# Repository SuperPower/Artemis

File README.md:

# SuperPower
Here you should find the best power supplies for your low-power projects. Because of different requirements for an Raspberry Pi and micro-controllers like the ESP32 we split the project into two boards, one for the Raspberry Pi (SuperPower-Rpi) and one for micro-controllers (SuperPower-uC) with low power.

##### [SuperPower-Rpi](/SuperPower-RPi/) for Raspberry Pi

##### [SuperPower-uC](https://github.com/SuperPower) for micro-controllers and low-power devices

## Licence

All hardware designs and products you can find in this repository is licensed under [CERN Open Hardware Licence Version 2 - Weakly Reciprocal](/LICENCE.txt)

## Relevant links

[Discord Channel](https://discord.gg/dCr86Hk)  

[Google Drive Project Files](https://drive.google.com/drive/folders/1lCirijHUkISdUYBIRblkILHM6fstifWS)

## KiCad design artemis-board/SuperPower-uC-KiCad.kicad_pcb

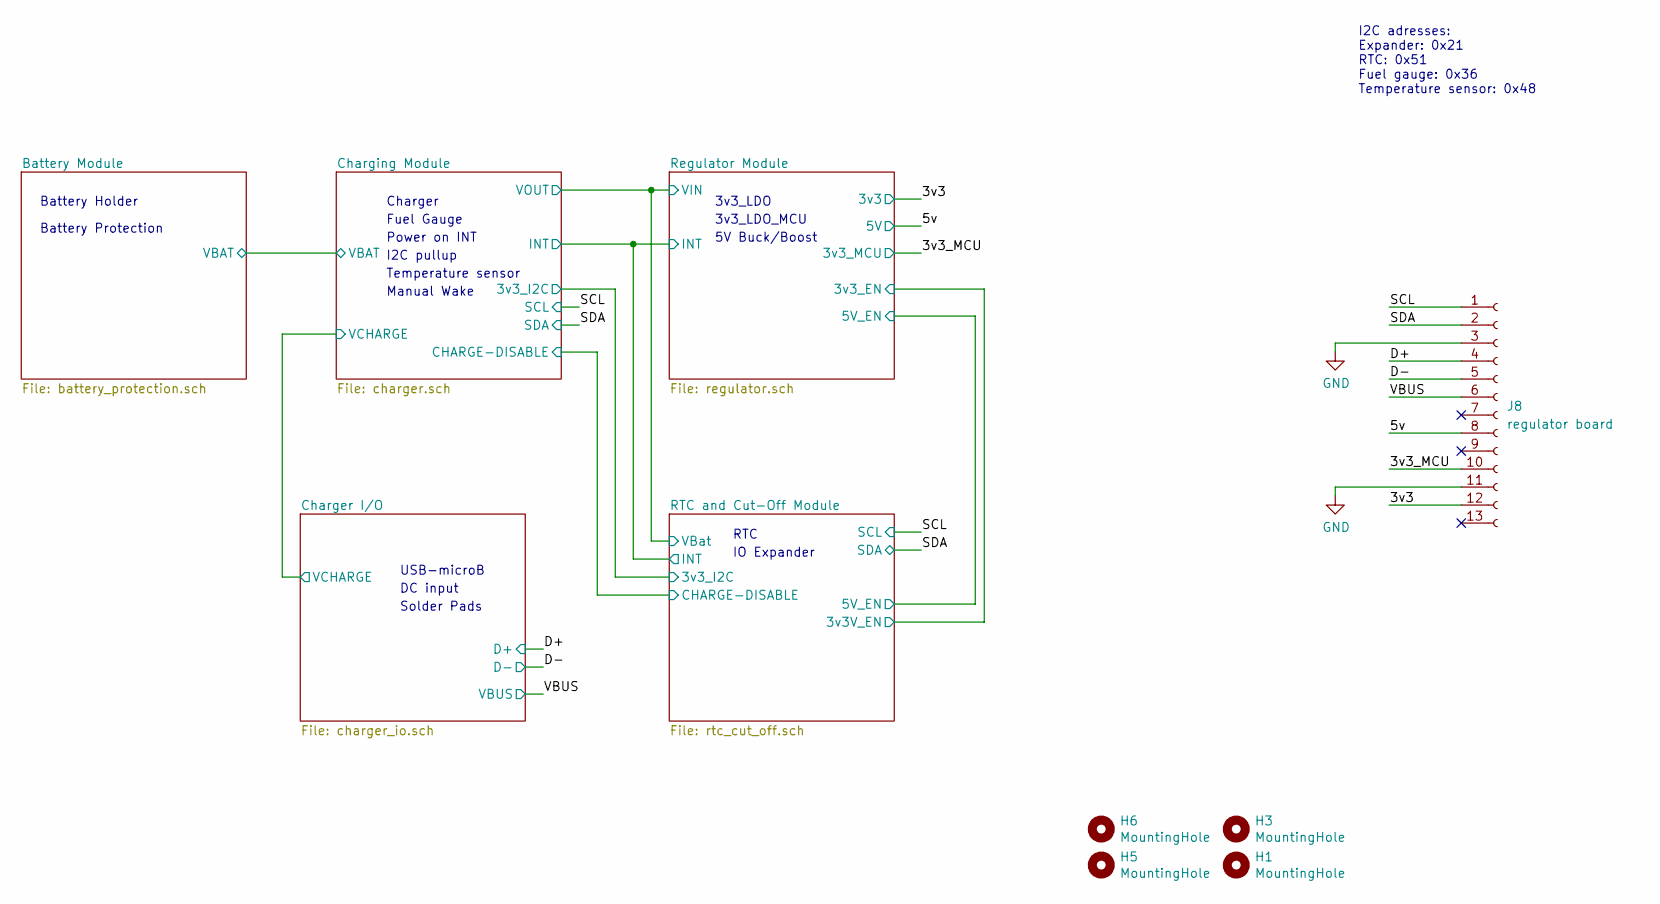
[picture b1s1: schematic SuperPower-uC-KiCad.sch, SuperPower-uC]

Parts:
H1, H3, H5, H6: MountingHole; MountingHole_2.7mm_M2.5_ISO7380
J8: regulator board; PinSocket_1x13_P2.54mm_Vertical; LCSC C52709

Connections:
/3v3: J8.12; also elsewhere on the board
/3v3_MCU: J8.10; also elsewhere on the board
/5v: J8.8; also elsewhere on the board
/D+: J8.4; also elsewhere on the board
/D-: J8.5; also elsewhere on the board
/SCL: J8.1; also elsewhere on the board
/SDA: J8.2; also elsewhere on the board
/VBUS: J8.6; also elsewhere on the board
GND: J8.3, J8.11; also elsewhere on the board

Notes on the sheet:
Battery Holder
Battery Protection
Charger
Fuel Gauge
3v3_LDO
3v3_LDO_MCU
5V Buck/Boost
RTC
USB-microB
DC input
Solder Pads
Manual Wake
Power on INT
IO Expander
I2C pullup
I2C adresses: Expander: 0x21 RTC: 0x51 Fuel gauge: 0x36 Temperature sensor: 0x48
Temperature sensor

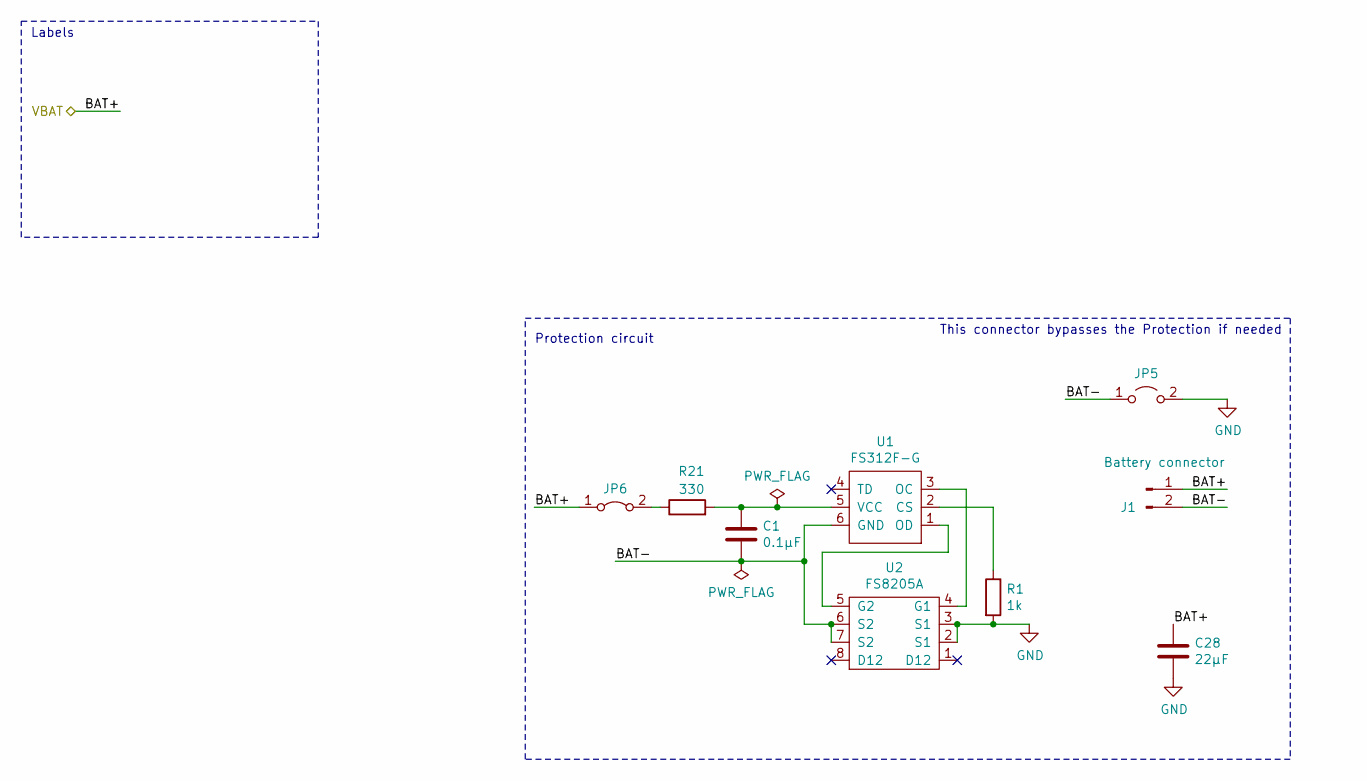
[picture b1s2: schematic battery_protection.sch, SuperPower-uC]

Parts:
C1: 0.1µF; C_0603_1608Metric_Pad1.05x0.95mm_HandSolder; LCSC C14858
C28: 22µF; C_0805_2012Metric; LCSC C45783
J1: Battery connector; JST_PH_S2B-PH-K_1x02_P2.00mm_Horizontal; LCSC C157932
JP5: Jumper_2_Open; SolderJumper-2_P1.3mm_Open_Pad1.0x1.5mm
JP6: Jumper_2_Bridged; SolderJumper-2_P1.3mm_Bridged_Pad1.0x1.5mm
R1: 1k; R_0603_1608Metric_Pad1.05x0.95mm_HandSolder; LCSC C21190
R21: 330; R_0603_1608Metric_Pad1.05x0.95mm_HandSolder; LCSC C23138
U1: FS312F-G; SOT-23-6; LCSC C82736
U2: FS8205A; TSSOP-8_4.4x3mm_P0.65mm; LCSC C16052

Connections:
/Battery Module/BAT-: C1.2, J1.2, JP5.1 (A), U1.6 (GND), U2.6 (S2), U2.7 (S2)
/Battery Module/VBAT: C28.1, J1.1, JP6.1 (A); also elsewhere on the board
GND: C28.2, JP5.2 (B), R1.2, U2.2 (S1), U2.3 (S1); also elsewhere on the board
unnamed: C1.1, R21.2, U1.5 (VCC)
unnamed: JP6.2 (B), R21.1
unnamed: R1.1, U1.2 (CS)
unnamed: U1.1 (OD), U2.5 (G2)
unnamed: U1.3 (OC), U2.4 (G1)

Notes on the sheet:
Protection circuit
Labels
This connector bypasses the Protection if needed

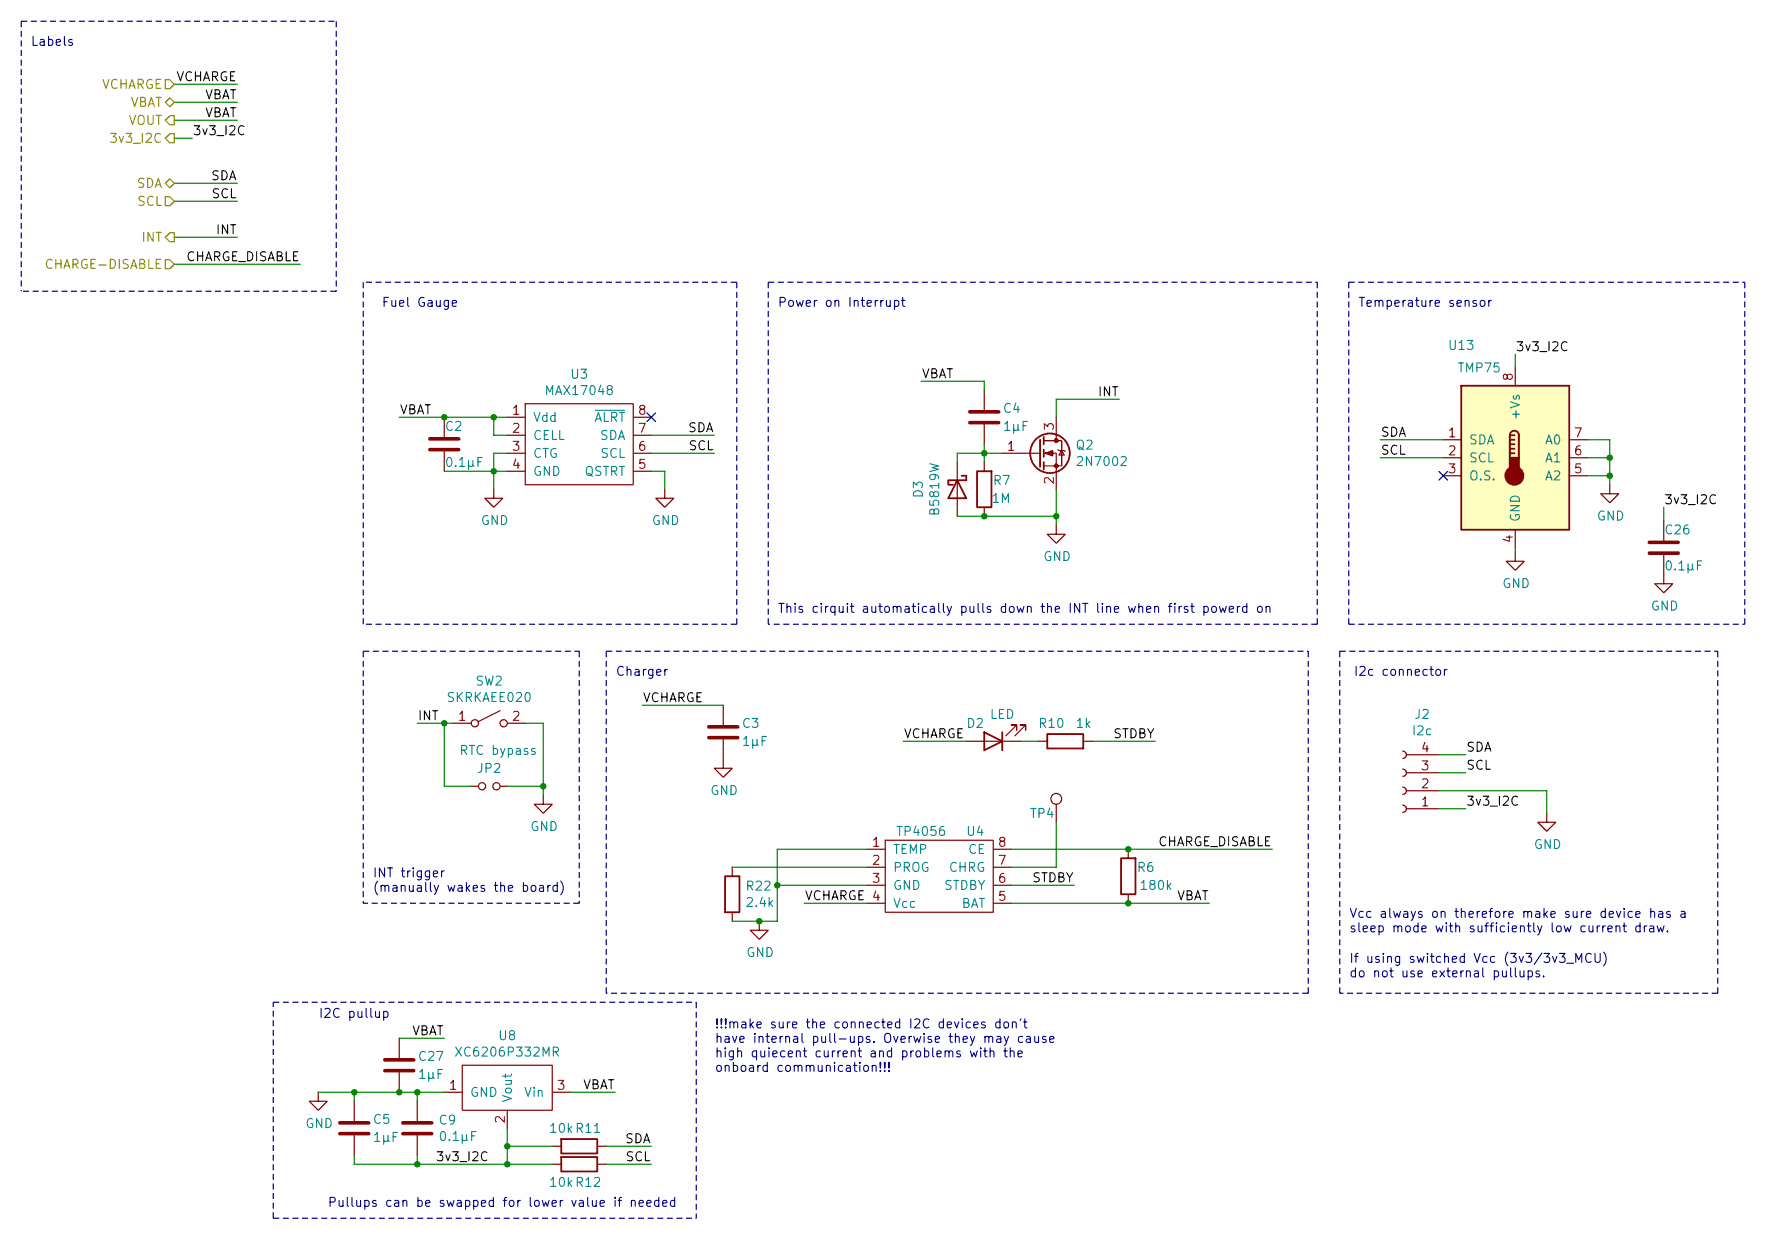
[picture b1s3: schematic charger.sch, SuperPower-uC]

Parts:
C2, C9, C26: 0.1µF; C_0603_1608Metric_Pad1.05x0.95mm_HandSolder; LCSC C14858
C3, C4, C5, C27: 1µF; C_0603_1608Metric_Pad1.08x0.95mm_HandSolder; LCSC C15849
D2: LED; LED_0603_1608Metric_Pad1.05x0.95mm_HandSolder; LCSC C72041
D3: B5819W; D_SOD-123; LCSC C8598
J2: I2c; PinSocket_1x04_P2.54mm_Vertical
JP2: RTC bypass; PinHeader_1x02_P2.54mm_Vertical
Q2: 2N7002; SOT-23; LCSC C8545
R6: 180k; R_0603_1608Metric_Pad1.05x0.95mm_HandSolder; LCSC C22827
R7: 1M; R_0603_1608Metric_Pad0.98x0.95mm_HandSolder; LCSC C22935
R10: 1k; R_0603_1608Metric_Pad1.05x0.95mm_HandSolder; LCSC C21190
R11, R12: 10k; R_0603_1608Metric_Pad1.05x0.95mm_HandSolder; LCSC C25804
R22: 2.4k; R_0603_1608Metric_Pad1.05x0.95mm_HandSolder; LCSC C22940
SW2: SKRKAEE020; SW_Push_SPST_NO_Alps_SKRK; LCSC C115357
TP4: TestPoint; TestPoint_Pad_1.5x1.5mm
U3: MAX17048; TDFN-8-1EP_2x2mm_P0.5mm_EP0.8x1.2mm; LCSC C2682616
U4: TP4056; SOP-8_3.9x4.9mm_P1.27mm; LCSC C16581
U8: XC6206P332MR; SOT-23; LCSC C5446
U13: TMP75; SOIC-8_3.9x4.9mm_P1.27mm; LCSC C30389

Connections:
/Battery Module/VBAT: C2.1, C4.1, C27.1, R6.1, U3.1 (Vdd), U3.2 (CELL), U4.5 (BAT), U8.3 (Vin); also elsewhere on the board
/Charger I/O/VCHARGE: C3.1, D2.2 (A), U4.4 (Vcc); also elsewhere on the board
/Charging Module/3v3_I2C: C5.2, C9.2, C26.1, J2.1, R11.2, R12.2, U8.2 (Vout), U13.8 (+Vs); also elsewhere on the board
/Charging Module/CHARGE-DISABLE: R6.2, U4.8 (CE); also elsewhere on the board
/Charging Module/INT: JP2.2, Q2.3 (D), SW2.1 (A); also elsewhere on the board
/Charging Module/STDBY: R10.2, U4.6 (STDBY)
/SCL: J2.3, R12.1, U3.6 (SCL), U13.2 (SCL); also elsewhere on the board
/SDA: J2.4, R11.1, U3.7 (SDA), U13.1 (SDA); also elsewhere on the board
GND: C2.2, C3.2, C5.1, C9.1, C26.2, C27.2, D3.2 (A), J2.2, JP2.1, Q2.2 (S), R7.1, R22.2, SW2.2 (B), U3.3 (CTG), U3.4 (GND), U3.5 (QSTRT), U4.1 (TEMP), U4.3 (GND), U8.1 (GND), U13.4 (GND), U13.5 (A2), U13.6 (A1), U13.7 (A0); also elsewhere on the board
unnamed: C4.2, D3.1 (K), Q2.1 (G), R7.2
unnamed: D2.1 (K), R10.1
unnamed: R22.1, U4.2 (PROG)
unnamed: TP4.1, U4.7 (CHRG)

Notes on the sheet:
Power on Interrupt
Charger
Fuel Gauge
Labels
This cirquit automatically pulls down the INT line when first powerd on
INT trigger (manually wakes the board)
Pullups can be swapped for lower value if needed
!!!make sure the connected I2C devices don't have internal pull-ups. Overwise they may cause high quiecent current and problems with the onboard communication!!!
I2C pullup
I2c connector
Temperature sensor
Vcc always on therefore make sure device has a sleep mode with sufficiently low current draw.
If using switched Vcc (3v3/3v3_MCU) do not use external pullups.

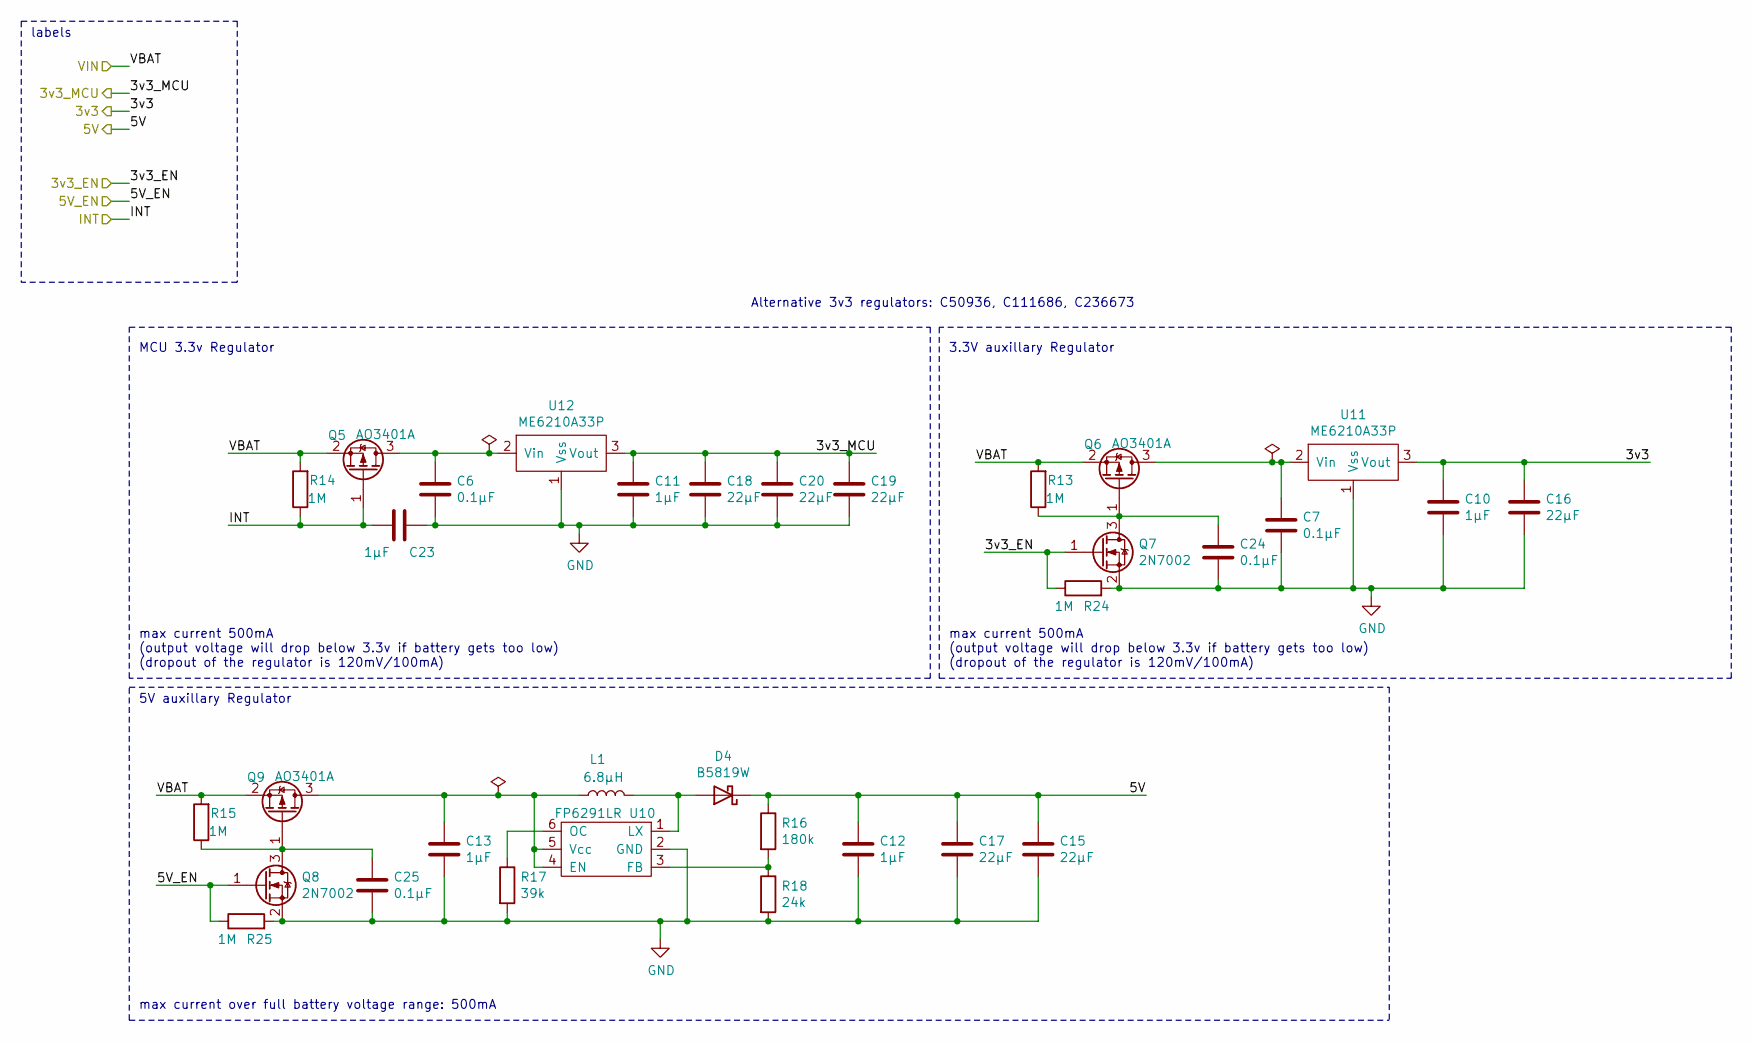
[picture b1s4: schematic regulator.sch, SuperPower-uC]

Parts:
C6, C7, C24, C25: 0.1µF; C_0603_1608Metric_Pad1.05x0.95mm_HandSolder; LCSC C14858
C10, C11, C12, C13, C23: 1µF; C_0603_1608Metric_Pad1.08x0.95mm_HandSolder; LCSC C15849
C15, C16, C17, C18, C19, C20: 22µF; C_0805_2012Metric; LCSC C45783
D4: B5819W; D_SOD-123; LCSC C8598
L1: 6.8µH; L_Bourns_SRP7028A_7.3x6.6mm; LCSC C207841
Q5, Q6, Q9: AO3401A; SOT-23; LCSC C15127
Q7, Q8: 2N7002; SOT-23; LCSC C8545
R13, R14, R15, R24, R25: 1M; R_0603_1608Metric_Pad0.98x0.95mm_HandSolder; LCSC C22935
R16: 180k; R_0603_1608Metric_Pad1.05x0.95mm_HandSolder; LCSC C22827
R17: 39k; R_0603_1608Metric_Pad1.05x0.95mm_HandSolder; LCSC C23153
R18: 24k; R_0603_1608Metric_Pad1.05x0.95mm_HandSolder; LCSC C23352
U10: FP6291LR; SOT-23-6; LCSC C18701
U11, U12: ME6210A33P; SOT-89-3; LCSC C85233

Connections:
/3v3: C10.1, C16.1, U11.3 (Vout); also elsewhere on the board
/3v3_MCU: C11.1, C18.1, C19.1, C20.1, U12.3 (Vout); also elsewhere on the board
/5v: C12.1, C15.1, C17.1, D4.1 (K), R16.1; also elsewhere on the board
/Battery Module/VBAT: Q5.2 (S), Q6.2 (S), Q9.2 (S), R13.2, R14.2, R15.2; also elsewhere on the board
/Charging Module/INT: C23.2, Q5.1 (G), R14.1; also elsewhere on the board
/RTC and Cut-Off Module/3v3V_EN: Q7.1 (G), R24.1; also elsewhere on the board
/RTC and Cut-Off Module/5V_EN: Q8.1 (G), R25.1; also elsewhere on the board
GND: C6.2, C7.2, C10.2, C11.2, C12.2, C13.2, C15.2, C16.2, C17.2, C18.2, C19.2, C20.2, C23.1, C24.2, C25.2, Q7.2 (S), Q8.2 (S), R17.2, R18.2, R24.2, R25.2, U10.2 (GND), U11.1 (Vss), U12.1 (Vss); also elsewhere on the board
unnamed: C6.1, Q5.3 (D), U12.2 (Vin)
unnamed: C7.1, Q6.3 (D), U11.2 (Vin)
unnamed: C13.1, L1.1, Q9.3 (D), U10.4 (EN), U10.5 (Vcc)
unnamed: C24.1, Q6.1 (G), Q7.3 (D), R13.1
unnamed: C25.1, Q8.3 (D), Q9.1 (G), R15.1
unnamed: D4.2 (A), L1.2, U10.1 (LX)
unnamed: R16.2, R18.1, U10.3 (FB)
unnamed: R17.1, U10.6 (OC)

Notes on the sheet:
MCU 3.3v Regulator
3.3V auxillary Regulator
5V auxillary Regulator
labels
Alternative 3v3 regulators: C50936, C111686, C236673
max current over full battery voltage range: 500mA
max current 500mA (output voltage will drop below 3.3v if battery gets too low) (dropout of the regulator is 120mV/100mA)

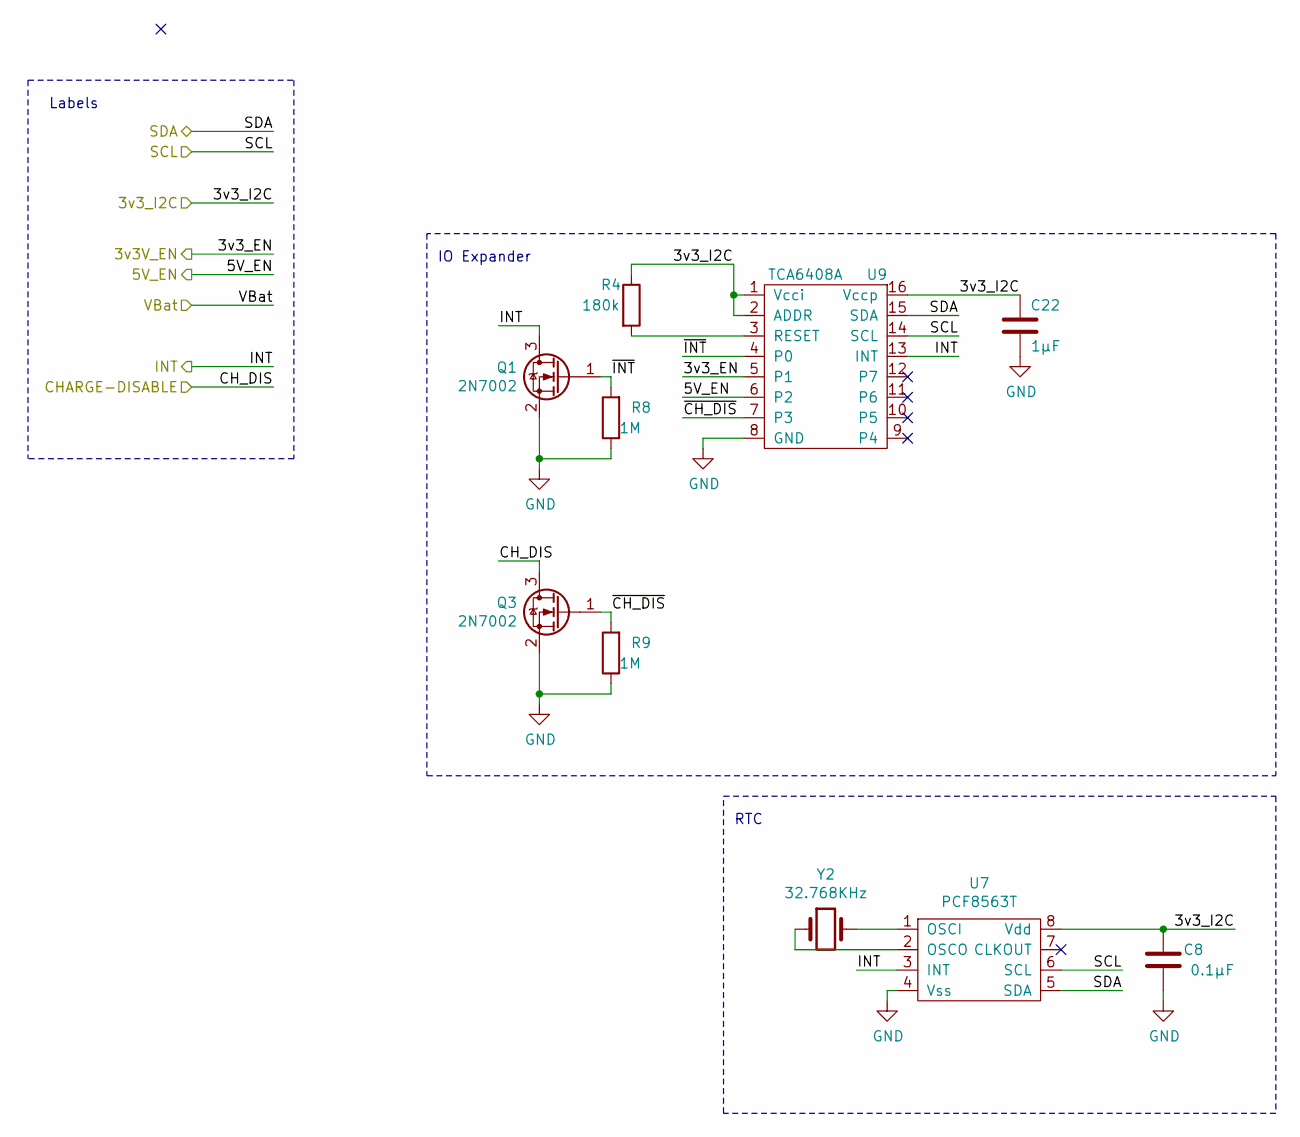
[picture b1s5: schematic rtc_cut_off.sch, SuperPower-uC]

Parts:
C8: 0.1µF; C_0603_1608Metric_Pad1.05x0.95mm_HandSolder; LCSC C14858
C22: 1µF; C_0603_1608Metric_Pad1.08x0.95mm_HandSolder; LCSC C15849
Q1, Q3: 2N7002; SOT-23; LCSC C8545
R4: 180k; R_0603_1608Metric_Pad1.05x0.95mm_HandSolder; LCSC C22827
R8, R9: 1M; R_0603_1608Metric_Pad0.98x0.95mm_HandSolder; LCSC C22935
U7: PCF8563T; SOIC-8_3.9x4.9mm_P1.27mm; LCSC C7440
U9: TCA6408A; TSSOP-16_4.4x5mm_P0.65mm; LCSC C206177
Y2: 32.768KHz; Crystal_SMD_3215-2Pin_3.2x1.5mm; LCSC C32346

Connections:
/Charging Module/3v3_I2C: C8.2, C22.2, R4.1, U7.8 (Vdd), U9.1 (Vcci), U9.2 (ADDR), U9.16 (Vccp); also elsewhere on the board
/Charging Module/CHARGE-DISABLE: Q3.3 (D); also elsewhere on the board
/Charging Module/INT: Q1.3 (D), U7.3 (INT), U9.13 (INT); also elsewhere on the board
/RTC and Cut-Off Module/3v3V_EN: U9.5 (P1); also elsewhere on the board
/RTC and Cut-Off Module/5V_EN: U9.6 (P2); also elsewhere on the board
/RTC and Cut-Off Module/~CH_DIS: Q3.1 (G), R9.2, U9.7 (P3)
/RTC and Cut-Off Module/~INT: Q1.1 (G), R8.2, U9.4 (P0)
/SCL: U7.6 (SCL), U9.14 (SCL); also elsewhere on the board
/SDA: U7.5 (SDA), U9.15 (SDA); also elsewhere on the board
GND: C8.1, C22.1, Q1.2 (S), Q3.2 (S), R8.1, R9.1, U7.4 (Vss), U9.8 (GND); also elsewhere on the board
unnamed: R4.2, U9.3 (RESET)
unnamed: U7.1 (OSCI), Y2.2
unnamed: U7.2 (OSCO), Y2.1

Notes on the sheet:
Labels
RTC
IO Expander

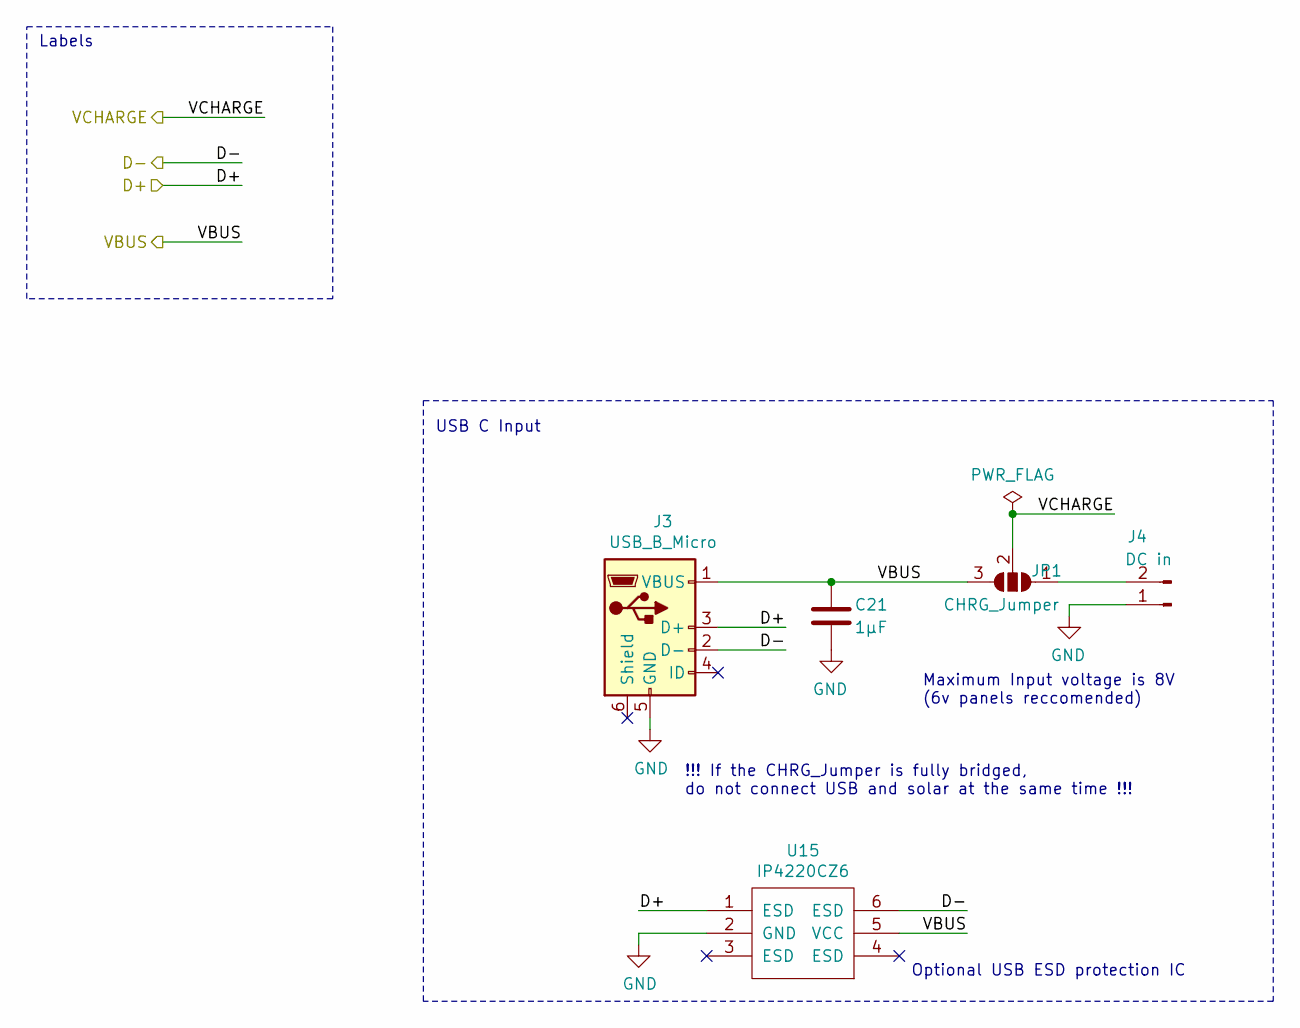
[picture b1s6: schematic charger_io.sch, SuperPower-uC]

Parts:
C21: 1µF; C_0603_1608Metric_Pad1.08x0.95mm_HandSolder; LCSC C15849
J3: USB_B_Micro; USB_Micro-B_Molex-105017-0001; LCSC C404969
J4: DC in; JST_EH_S2B-EH_1x02_P2.50mm_Horizontal; LCSC C225424
JP1: CHRG_Jumper; SolderJumper-3_P1.3mm_Open_Pad1.0x1.5mm
U15: IP4220CZ6; TSOP-6_1.65x3.05mm_P0.95mm

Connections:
/Charger I/O/VCHARGE: JP1.2 (C); also elsewhere on the board
/D+: J3.3 (D+), U15.1 (ESD); also elsewhere on the board
/D-: J3.2 (D-), U15.6 (ESD); also elsewhere on the board
/VBUS: C21.1, J3.1 (VBUS), JP1.3 (B), U15.5 (VCC); also elsewhere on the board
GND: C21.2, J3.5 (GND), J4.1, U15.2 (GND); also elsewhere on the board
unnamed: J4.2, JP1.1 (A)

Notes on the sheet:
USB C Input
Labels
Maximum Input voltage is 8V (6v panels reccomended)
!!! If the CHRG_Jumper is fully bridged, do not connect USB and solar at the same time !!!
Optional USB ESD protection IC

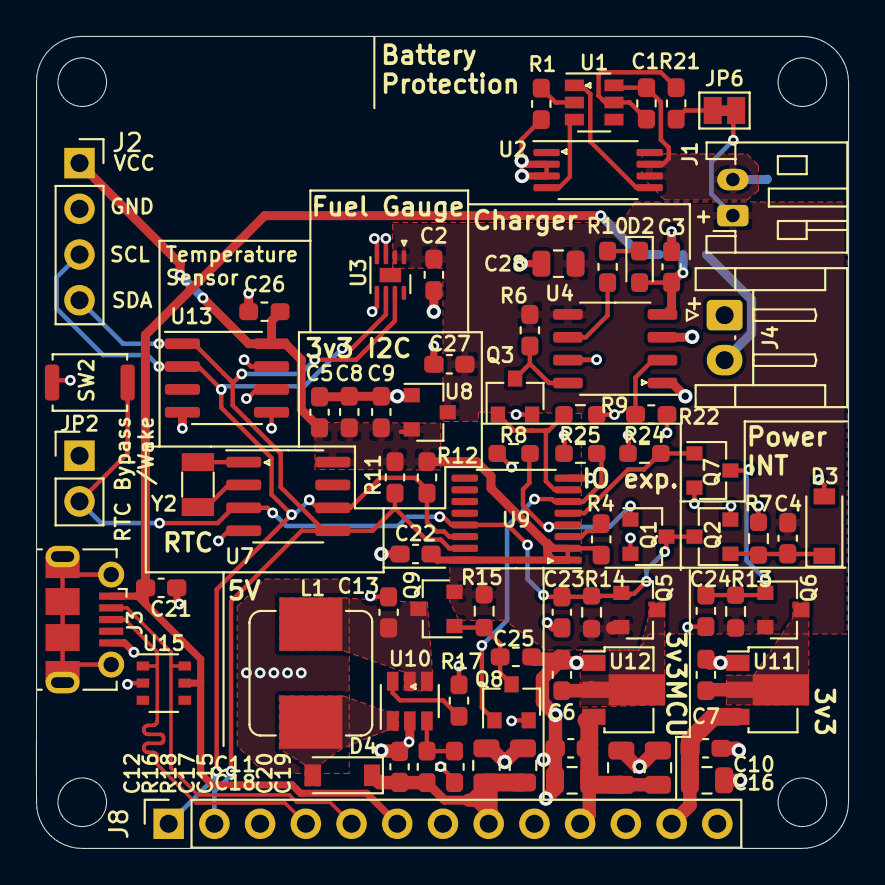
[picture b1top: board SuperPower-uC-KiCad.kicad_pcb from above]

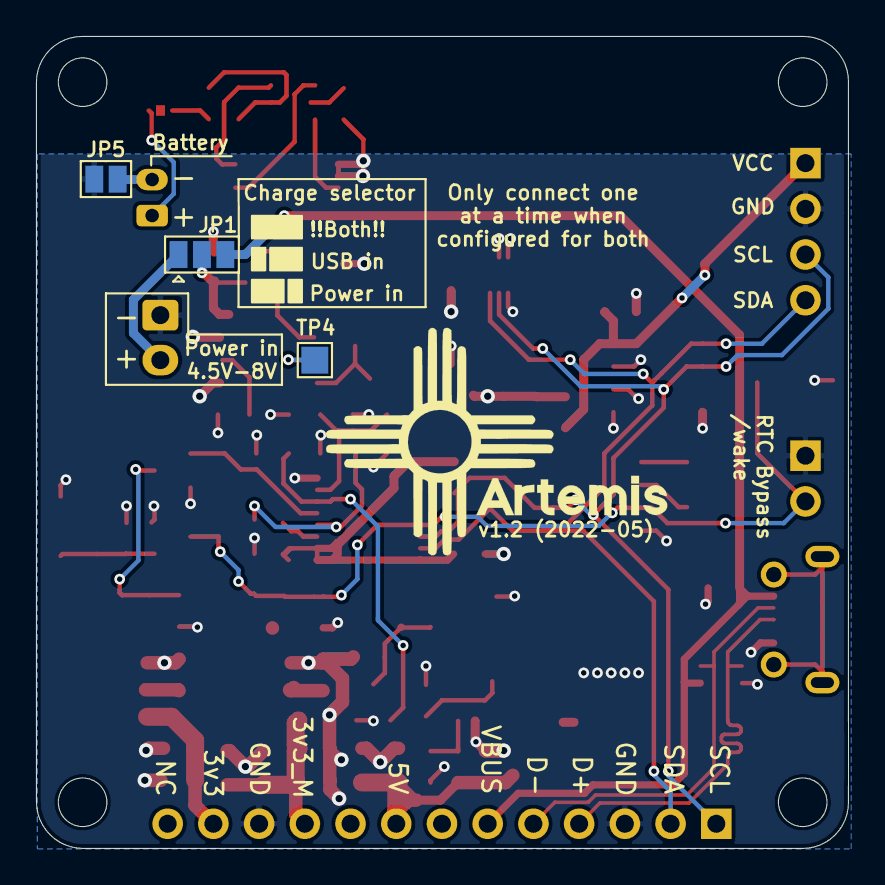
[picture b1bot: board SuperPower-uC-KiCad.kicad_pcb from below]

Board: 4 copper layers, 45.1 x 45.1 mm, 86 parts (3 on the bottom side), 41 nets.

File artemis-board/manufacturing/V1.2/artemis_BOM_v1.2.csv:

Comment,Designator,Footprint,LCSC,Optional
0.1µF,"C1,C2,C6,C7,C8,C9,C24,C25,C26",Capacitor_SMD:C_0603_1608Metric_Pad1.05x0.95mm_HandSolder,C14858,
22µF,"C15,C16,C17,C18,C19,C20,C28",Capacitor_SMD:C_0805_2012Metric,C45783,
1µF,"C3,C4,C5,C10,C11,C12,C13,C21,C22,C23,C27",Capacitor_SMD:C_0603_1608Metric_Pad1.08x0.95mm_HandSolder,C15849,
LED,D2,LED_SMD:LED_0603_1608Metric_Pad1.05x0.95mm_HandSolder,C72041,
B5819W,"D3,D4",Diode_SMD:D_SOD-123,C8598,
Battery connector,J1,Connector_JST:JST_PH_S2B-PH-K_1x02_P2.00mm_Horizontal,C157932,yes
USB_B_Micro,J3,Connector_USB:USB_Micro-B_Molex-105017-0001,C404969,
DC in,J4,Connector_JST:JST_EH_S2B-EH_1x02_P2.50mm_Horizontal,C225424,yes
regulator board,J8,Connector_PinSocket_2.54mm:PinSocket_1x13_P2.54mm_Vertical,C52709,yes
6.8µH,L1,Inductor_SMD:L_Bourns_SRP7028A_7.3x6.6mm,C207841,
2N7002,"Q1,Q2,Q3,Q7,Q8",Package_TO_SOT_SMD:SOT-23,C8545,
AO3401A,"Q5,Q6,Q9",Package_TO_SOT_SMD:SOT-23,C15127,
1k,"R1,R10",Resistor_SMD:R_0603_1608Metric_Pad1.05x0.95mm_HandSolder,C21190,
10k,"R11,R12",Resistor_SMD:R_0603_1608Metric_Pad1.05x0.95mm_HandSolder,C25804,
39k,R17,Resistor_SMD:R_0603_1608Metric_Pad1.05x0.95mm_HandSolder,C23153,
24k,R18,Resistor_SMD:R_0603_1608Metric_Pad1.05x0.95mm_HandSolder,C23352,
330,R21,Resistor_SMD:R_0603_1608Metric_Pad1.05x0.95mm_HandSolder,C23138,
2.4k,R22,Resistor_SMD:R_0603_1608Metric_Pad1.05x0.95mm_HandSolder,C22940,
180k,"R4,R6,R16",Resistor_SMD:R_0603_1608Metric_Pad1.05x0.95mm_HandSolder,C22827,
1M,"R7,R8,R9,R13,R14,R15,R24,R25",Resistor_SMD:R_0603_1608Metric_Pad0.98x0.95mm_HandSolder,C22935,
SKRKAEE020,SW2,Button_Switch_SMD:SW_Push_SPST_NO_Alps_SKRK,C115357,yes
FS312F-G,U1,Package_TO_SOT_SMD:SOT-23-6,C82736,
FP6291LR,U10,Package_TO_SOT_SMD:SOT-23-6,C18701,
ME6210A33P,"U11,U12",Package_TO_SOT_SMD:SOT-89-3,C85233,
TMP75,U13,Package_SO:SOIC-8_3.9x4.9mm_P1.27mm,C30389,
IP4220CZ6,U15,Package_SO:TSOP-6_1.65x3.05mm_P0.95mm,,
FS8205A,U2,Package_SO:TSSOP-8_4.4x3mm_P0.65mm,C16052,
MAX17048,U3,Package_DFN_QFN:TDFN-8-1EP_2x2mm_P0.5mm_EP0.8x1.2mm,C2682616,
TP4056,U4,Package_SO:SOP-8_3.9x4.9mm_P1.27mm,C16581,
PCF8563T,U7,Package_SO:SOIC-8_3.9x4.9mm_P1.27mm,C7440,
XC6206P332MR,U8,Package_TO_SOT_SMD:SOT-23,C5446,
TCA6408A,U9,Package_SO:TSSOP-16_4.4x5mm_P0.65mm,C206177,
32.768KHz,Y2,Crystal:Crystal_SMD_3215-2Pin_3.2x1.5mm,C32346,

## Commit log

2021-02-21 Move Repo and reduce project files to only contain the Artemis Board
2021-02-22 renamed net lables, disconnected en lines from header and deleted unused
2021-02-24 increased output caps of voltage regulators
2021-02-25 added library and sample code
2021-02-26 fixed silk placements
2021-03-05 re-add logo
2021-03-05 added part number for button
2021-03-08 fixed erc
2021-03-08 changed switch value
2021-03-27 updated TCA6408A symbol
2021-03-27 connected io expanders Vccp pin to Vbat instead of Vcc_I2c
2021-04-09 moved fuel gauge pin 1 marker to pin 1
2021-04-29 deleted unused lines in sample code
2021-05-01 fixed brackets in time get functions
2021-05-03 added set alarm functions
2021-05-03 consolidated sleep_minutes and sleep_seconds into 1 function
2021-05-03 added charge disable function and fixed minor mistakes
2021-05-03 updated sample code and applied fixes
2021-05-04 fixed problem with TF not being reset before going to sleep
2021-05-15 swapped R15 for 24k
2021-05-15 added pulldown to Q1 and inverter to CH_DIS
2021-05-15 added cirquit to measure Vbat with esp in case of fuel gauge shortage
2021-05-15 annotated Q10
2021-05-15 applied changes to board
2021-05-16 modified sample sketch to correspond with the new sleep function
2021-05-17 removed unused net label
2021-05-19 swapped protection ic for the FS312F-G
2021-05-21 updated revision number
2021-05-24 added comment with alternative 3v3 regulators
2021-05-24 swapped switch for cheaper alps one
2021-05-25 changed the layout a bit and removed TP on boost converter
2021-05-25 increased value of R17 to decrease 5v overcurrent protection
2021-05-25 corrected inductor value text field
2021-05-27 cleanup and fixes
    fixed sleep not deactivating tie, cleanup in set_charge function, added some more comments
2021-05-28 moved Vbat/2 line to other pin on the header
2021-05-30 moved R8 and did some minor silk and routing changes
2021-05-31 added comments and swapped polarity of Vin connector
2021-06-01 added 1µ cap close to 3v3 I2C regulator
2021-06-06 swapped and added some lcsc part numbers and DNP markers
2021-06-07 added cap to Vbat rail for more stability
2021-06-15 renamed example
2021-06-20 fixed silk being moved on some caps
2021-06-24 added jumpers for use without io expander
2021-06-24 added comments for the jumpers and pulldowns for Q7 and Q8
2021-07-05 added warning comment for expander ic
2021-07-07 connected VccP of io expander back to 3v3, changed some footprint
    also added NMos so voltage divider can be used
2021-07-09 removed unprotected connector, added jumper, moved cap to 3v3_mcu
2021-07-11 added cap to 3v3 I2c, swapped some footprints to normal...
2021-07-12 removed voltage level warning for io expander due to Vccp on 3v3
2021-07-12 improved silk placement and routing
2021-07-15 added PCA9557 and swapped IO expander for it
2021-08-01 added WLCSP9 footprint for LC709203
2021-08-02 added datasheet for pca9557 and connected ~INT to another pin
2021-08-02 added link in sym-lib-table to PCA9557
2021-08-02 added production files
2021-08-10 alternative package for PCA9557 and smaller silk
2021-08-14 added reverse polarity protection to power input
2021-08-15 TSSOP version (different pins)
2021-09-05 created production files
    BOMv1 has components grouped BOMv2 does not
2022-02-03 organized production files
2022-04-27 removed lc709203 and added MAX17048
2022-04-28 + temperature sensor, i2c header - esp voltage measurement...
2022-04-28 added comments, part numbers and extended marker
2022-05-02 moved i2c and int connector to be on 2.54mm grid
2022-05-06 added manufacturing files

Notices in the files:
artemis-board/SuperPower-uC-KiCad.sch:
Licence: CERN-OHL-W
